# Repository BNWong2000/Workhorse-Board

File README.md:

# Workhorse-Board
Workhorse 3D printer controller board, intended for long term safe and reliable operation.

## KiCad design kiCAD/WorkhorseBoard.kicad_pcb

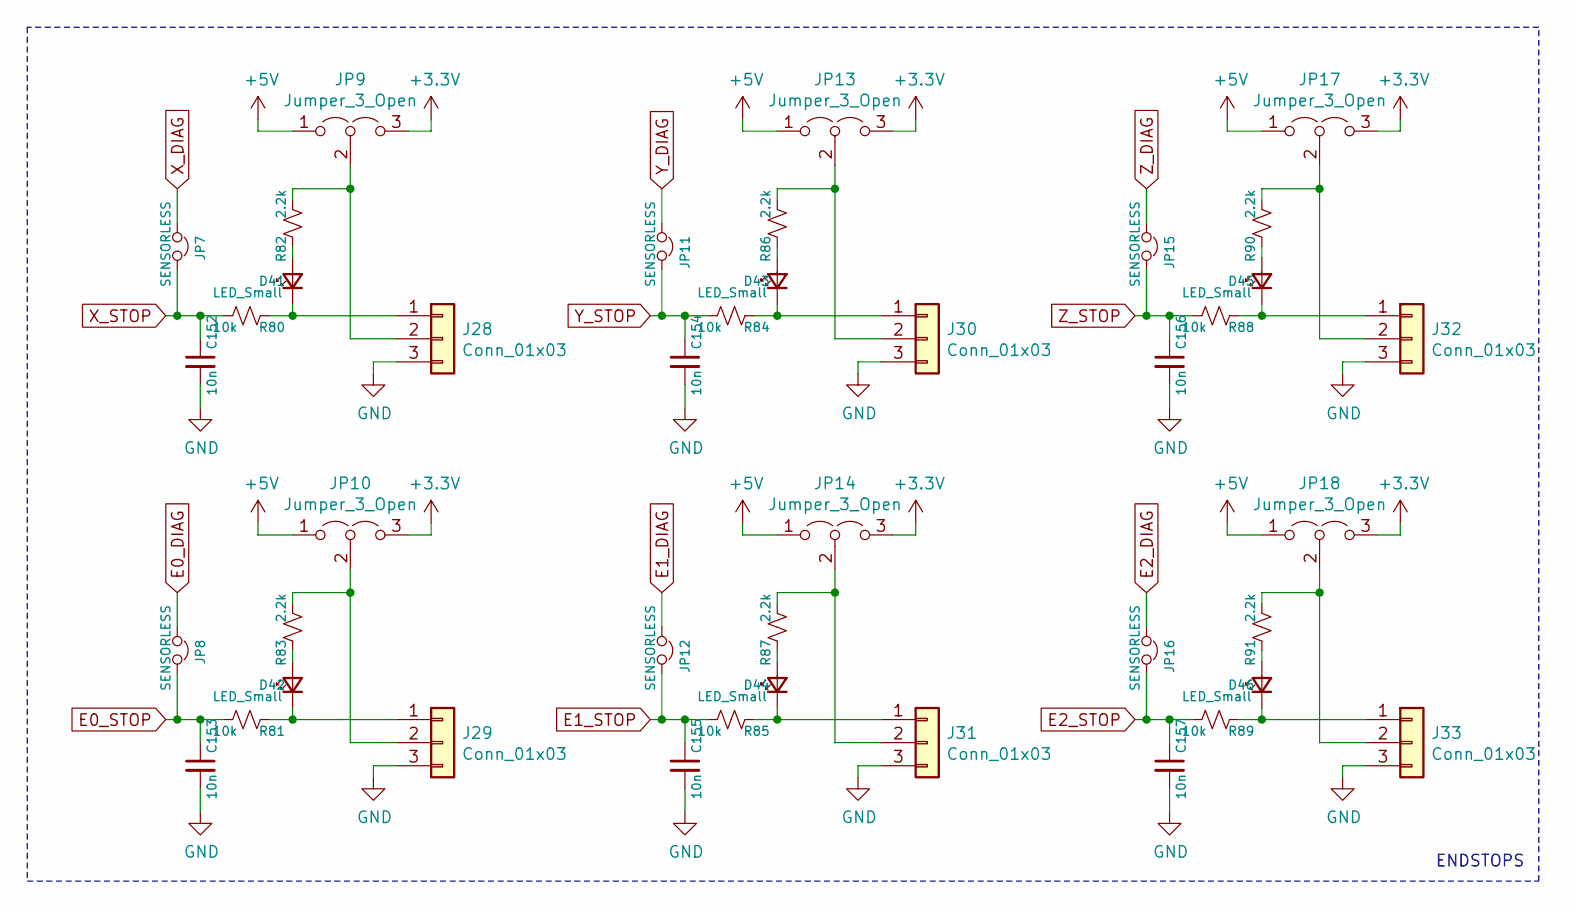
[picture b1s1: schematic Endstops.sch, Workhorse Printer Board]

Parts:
C152, C153, C154, C155, C156, C157: 10n; C_0603_1608Metric_Pad1.05x0.95mm_HandSolder
D41, D42, D43, D44, D45, D46: LED_Small; D_0603_1608Metric_Pad1.05x0.95mm_HandSolder
J28, J29, J30, J31, J32, J33: Conn_01x03; Molex_KK-254_AE-6410-03A_1x03_P2.54mm_Vertical
JP7, JP8, JP11, JP12, JP15, JP16: SENSORLESS; PinHeader_1x02_P2.54mm_Vertical
JP9, JP10, JP13, JP14, JP17, JP18: Jumper_3_Open; PinHeader_1x03_P2.54mm_Vertical
R80, R81, R84, R85, R88, R89: 10k; R_0603_1608Metric_Pad1.05x0.95mm_HandSolder
R82, R83, R86, R87, R90, R91: 2.2k; R_0603_1608Metric_Pad1.05x0.95mm_HandSolder

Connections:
+3V3: JP9.3 (B), JP10.3 (B), JP13.3 (B), JP14.3 (B), JP17.3 (B), JP18.3 (B); also elsewhere on the board
+5V: JP9.1 (A), JP10.1 (A), JP13.1 (A), JP14.1 (A), JP17.1 (A), JP18.1 (A); also elsewhere on the board
E0_DIAG: JP8.1; also elsewhere on the board
E0_STOP: C153.1, JP8.2, R81.2; also elsewhere on the board
E1_DIAG: JP12.1; also elsewhere on the board
E1_STOP: C155.1, JP12.2, R85.2; also elsewhere on the board
E2_DIAG: JP16.1; also elsewhere on the board
E2_STOP: C157.1, JP16.2, R89.2; also elsewhere on the board
GND: C152.2, C153.2, C154.2, C155.2, C156.2, C157.2, J28.3, J29.3, J30.3, J31.3, J32.3, J33.3; also elsewhere on the board
unnamed: D41.1 (K), J28.1, R80.1
unnamed: D41.2 (A), R82.1
unnamed: D42.1 (K), J29.1, R81.1
unnamed: D42.2 (A), R83.1
unnamed: D43.1 (K), J30.1, R84.1
unnamed: D43.2 (A), R86.1
unnamed: D44.1 (K), J31.1, R85.1
unnamed: D44.2 (A), R87.1
unnamed: D45.1 (K), J32.1, R88.1
unnamed: D45.2 (A), R90.1
unnamed: D46.1 (K), J33.1, R89.1
unnamed: D46.2 (A), R91.1
unnamed: J28.2, JP9.2 (C), R82.2
unnamed: J29.2, JP10.2 (C), R83.2
unnamed: J30.2, JP13.2 (C), R86.2
unnamed: J31.2, JP14.2 (C), R87.2
unnamed: J32.2, JP17.2 (C), R90.2
unnamed: J33.2, JP18.2 (C), R91.2
X_DIAG: JP7.1; also elsewhere on the board
X_STOP: C152.1, JP7.2, R80.2; also elsewhere on the board
Y_DIAG: JP11.1; also elsewhere on the board
Y_STOP: C154.1, JP11.2, R84.2; also elsewhere on the board
Z_DIAG: JP15.1; also elsewhere on the board
Z_STOP: C156.1, JP15.2, R88.2; also elsewhere on the board

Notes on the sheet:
ENDSTOPS

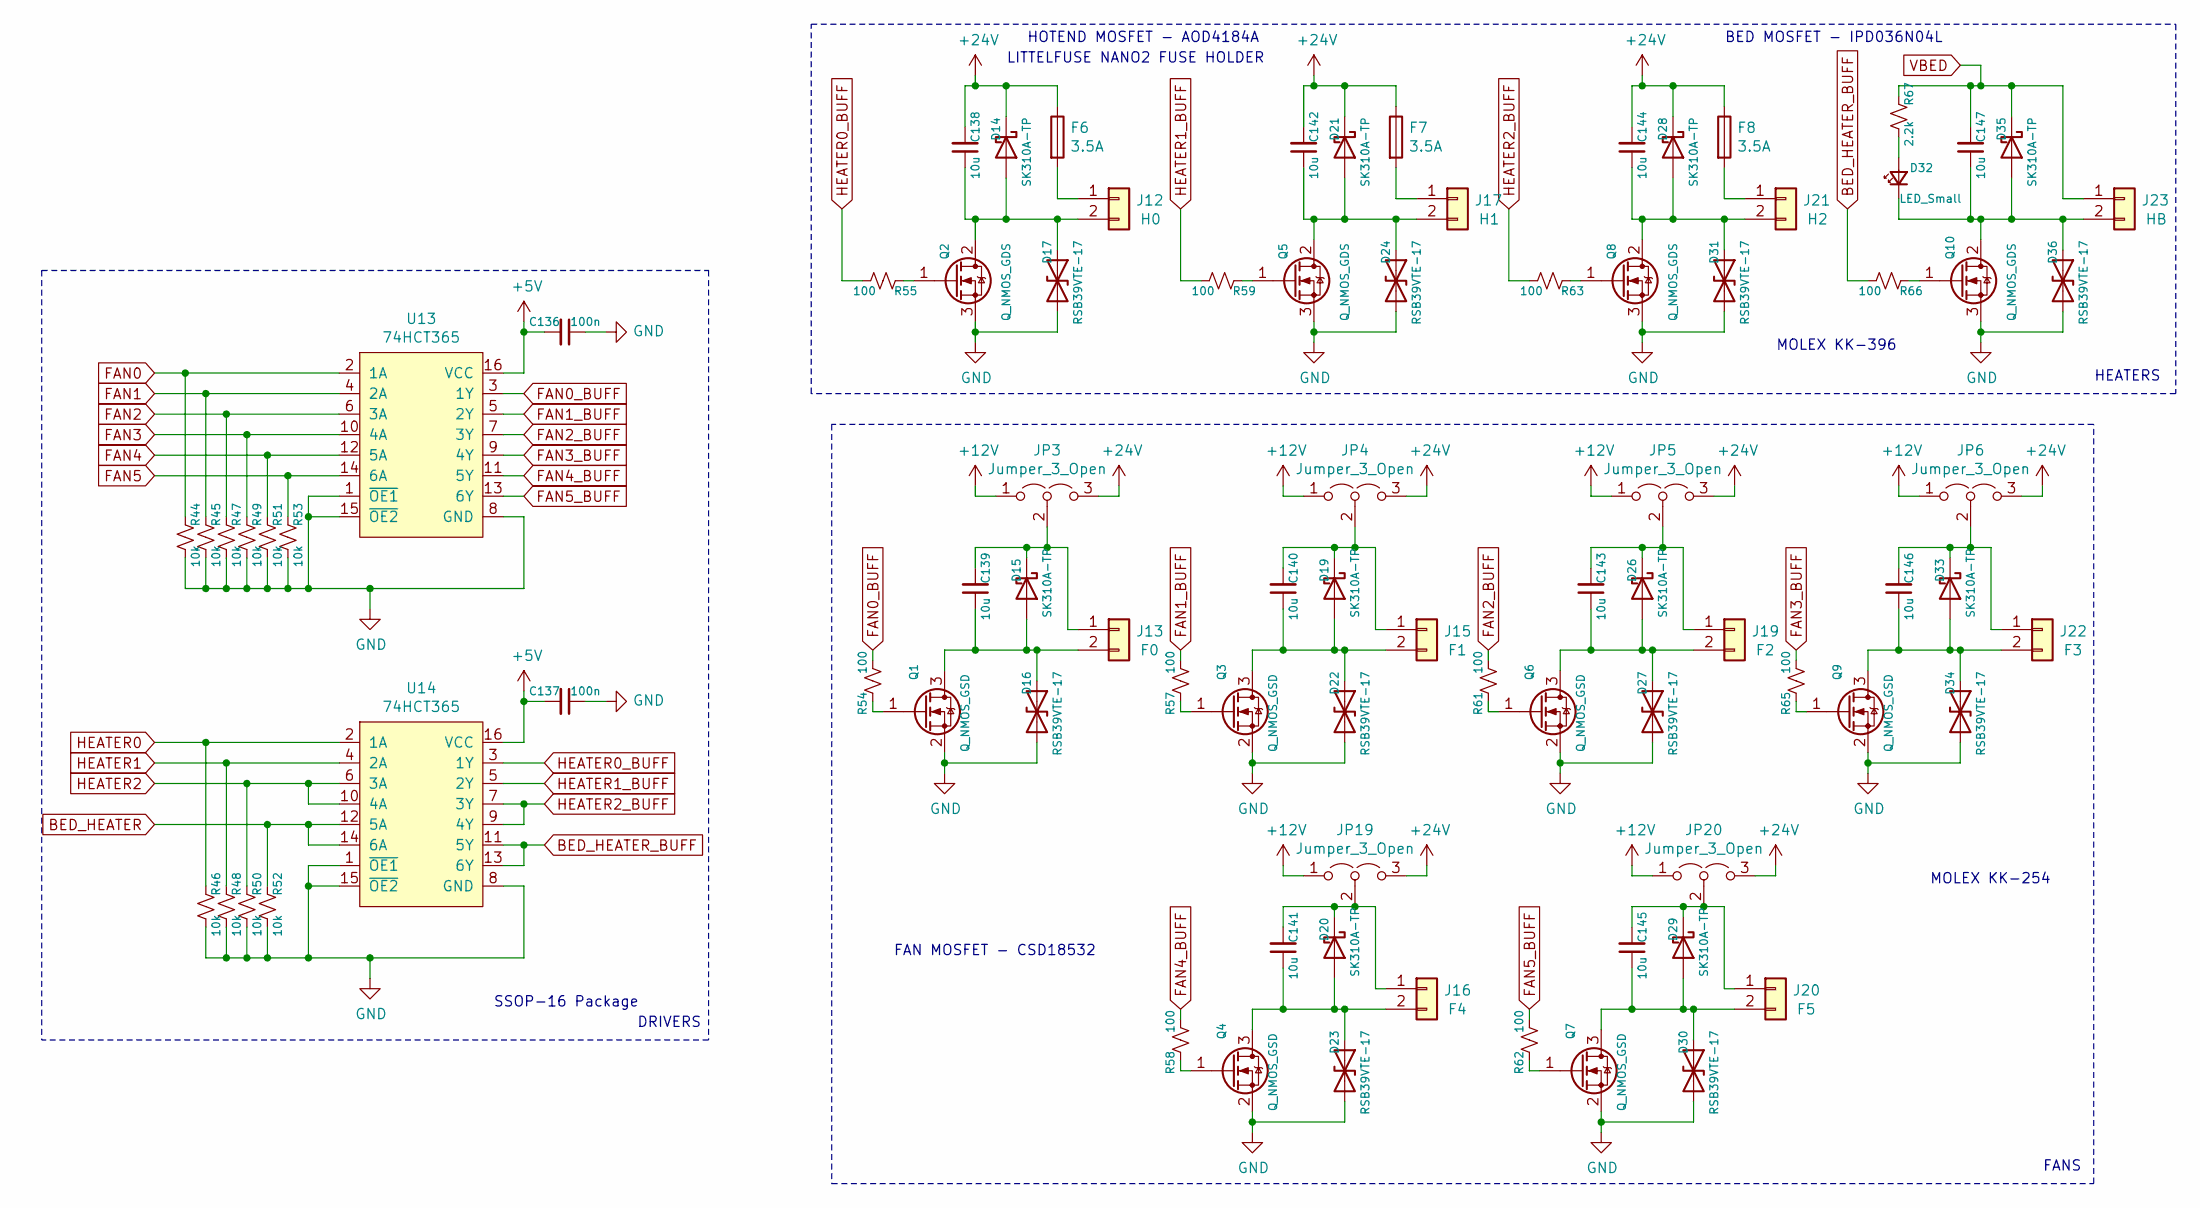
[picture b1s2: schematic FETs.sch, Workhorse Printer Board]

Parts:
C136, C137: 100n; C_0603_1608Metric_Pad1.05x0.95mm_HandSolder
C138, C139, C140, C141, C142, C143, C144, C145, C146, C147: 10u; C_1206_3216Metric_Pad1.42x1.75mm_HandSolder
D14, D15, D19, D20, D21, D26, D28, D29, D33, D35: SK310A-TP; D_SMA_Handsoldering
D16, D17, D22, D23, D24, D27, D30, D31, D34, D36: RSB39VTE-17; D_SOD-323F
D32: LED_Small; D_0603_1608Metric_Pad1.05x0.95mm_HandSolder
F6, F7, F8: 3.5A; Fuseholder_Littelfuse_Nano2_157x
J12: H0; Molex_KK-396_A-41791-0002_1x02_P3.96mm_Vertical
J13: F0; Molex_KK-254_AE-6410-02A_1x02_P2.54mm_Vertical
J15: F1; Molex_KK-254_AE-6410-02A_1x02_P2.54mm_Vertical
J16: F4; Molex_KK-254_AE-6410-02A_1x02_P2.54mm_Vertical
J17: H1; Molex_KK-396_A-41791-0002_1x02_P3.96mm_Vertical
J19: F2; Molex_KK-254_AE-6410-02A_1x02_P2.54mm_Vertical
J20: F5; Molex_KK-254_AE-6410-02A_1x02_P2.54mm_Vertical
J21: H2; Molex_KK-396_A-41791-0002_1x02_P3.96mm_Vertical
J22: F3; Molex_KK-254_AE-6410-02A_1x02_P2.54mm_Vertical
J23: HB; TerminalBlock_Dinkle_DT-55-B01X-02_P10.00mm
JP3, JP4, JP5, JP6, JP19, JP20: Jumper_3_Open; PinHeader_1x03_P2.54mm_Vertical
Q1, Q3, Q4, Q6, Q7, Q9: Q_NMOS_GSD; SOT-23_Handsoldering
Q2, Q5, Q8, Q10: Q_NMOS_GDS; TO-252-2
R44, R45, R46, R47, R48, R49, R50, R51, R52, R53: 10k; R_0603_1608Metric_Pad1.05x0.95mm_HandSolder
R54, R55, R57, R58, R59, R61, R62, R63, R65, R66: 100; R_0603_1608Metric_Pad1.05x0.95mm_HandSolder
R67: 2.2k; R_0603_1608Metric_Pad1.05x0.95mm_HandSolder
U13, U14: 74HCT365; SSOP-16_5.3x6.2mm_P0.65mm

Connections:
+5V: C136.2, C137.2, U13.16 (VCC), U14.16 (VCC); also elsewhere on the board
+12V: JP3.1 (A), JP4.1 (A), JP5.1 (A), JP6.1 (A), JP19.1 (A), JP20.1 (A); also elsewhere on the board
+24V: C138.2, C142.2, C144.2, D14.1 (K), D21.1 (K), D28.1 (K), F6.1, F7.1, F8.1, JP3.3 (B), JP4.3 (B), JP5.3 (B), JP6.3 (B), JP19.3 (B), JP20.3 (B); also elsewhere on the board
BED_HEATER: R52.1, U14.12 (5A), U14.14 (6A); also elsewhere on the board
BED_HEATER_BUFF: R66.2, U14.11 (5Y), U14.13 (6Y)
FAN0: R44.1, U13.2 (1A); also elsewhere on the board
FAN0_BUFF: R54.2, U13.3 (1Y)
FAN1: R45.1, U13.4 (2A); also elsewhere on the board
FAN1_BUFF: R57.2, U13.5 (2Y)
FAN2: R47.1, U13.6 (3A); also elsewhere on the board
FAN2_BUFF: R61.2, U13.7 (3Y)
FAN3: R49.1, U13.10 (4A); also elsewhere on the board
FAN3_BUFF: R65.2, U13.9 (4Y)
FAN4: R51.1, U13.12 (5A); also elsewhere on the board
FAN4_BUFF: R58.2, U13.11 (5Y)
FAN5: R53.1, U13.14 (6A); also elsewhere on the board
FAN5_BUFF: R62.2, U13.13 (6Y)
GND: C136.1, C137.1, D16.2 (A2), D17.2 (A2), D22.2 (A2), D23.2 (A2), D24.2 (A2), D27.2 (A2), D30.2 (A2), D31.2 (A2), D34.2 (A2), D36.2 (A2), Q1.2 (S), Q2.3 (S), Q3.2 (S), Q4.2 (S), Q5.3 (S), Q6.2 (S), Q7.2 (S), Q8.3 (S), Q9.2 (S), Q10.3 (S), R44.2, R45.2, R46.2, R47.2, R48.2, R49.2, R50.2, R51.2, R52.2, R53.2, U13.1 (~OE1), U13.8 (GND), U13.15 (~OE2), U14.1 (~OE1), U14.8 (GND), U14.15 (~OE2); also elsewhere on the board
HEATER0: R46.1, U14.2 (1A); also elsewhere on the board
HEATER0_BUFF: R55.2, U14.3 (1Y)
HEATER1: R48.1, U14.4 (2A); also elsewhere on the board
HEATER1_BUFF: R59.2, U14.5 (2Y)
HEATER2: R50.1, U14.6 (3A), U14.10 (4A); also elsewhere on the board
HEATER2_BUFF: R63.2, U14.7 (3Y), U14.9 (4Y)
unnamed: C138.1, D14.2 (A), D17.1 (A1), J12.2, Q2.2 (D)
unnamed: C139.1, D15.2 (A), D16.1 (A1), J13.2, Q1.3 (D)
unnamed: C139.2, D15.1 (K), J13.1, JP3.2 (C)
unnamed: C140.1, D19.2 (A), D22.1 (A1), J15.2, Q3.3 (D)
unnamed: C140.2, D19.1 (K), J15.1, JP4.2 (C)
unnamed: C141.1, D20.2 (A), D23.1 (A1), J16.2, Q4.3 (D)
unnamed: C141.2, D20.1 (K), J16.1, JP19.2 (C)
unnamed: C142.1, D21.2 (A), D24.1 (A1), J17.2, Q5.2 (D)
unnamed: C143.1, D26.2 (A), D27.1 (A1), J19.2, Q6.3 (D)
unnamed: C143.2, D26.1 (K), J19.1, JP5.2 (C)
unnamed: C144.1, D28.2 (A), D31.1 (A1), J21.2, Q8.2 (D)
unnamed: C145.1, D29.2 (A), D30.1 (A1), J20.2, Q7.3 (D)
unnamed: C145.2, D29.1 (K), J20.1, JP20.2 (C)
unnamed: C146.1, D33.2 (A), D34.1 (A1), J22.2, Q9.3 (D)
unnamed: C146.2, D33.1 (K), J22.1, JP6.2 (C)
unnamed: C147.1, D32.1 (K), D35.2 (A), D36.1 (A1), J23.2, Q10.2 (D)
unnamed: D32.2 (A), R67.2
unnamed: F6.2, J12.1
unnamed: F7.2, J17.1
unnamed: F8.2, J21.1
unnamed: Q1.1 (G), R54.1
unnamed: Q2.1 (G), R55.1
unnamed: Q3.1 (G), R57.1
unnamed: Q4.1 (G), R58.1
unnamed: Q5.1 (G), R59.1
unnamed: Q6.1 (G), R61.1
unnamed: Q7.1 (G), R62.1
unnamed: Q8.1 (G), R63.1
unnamed: Q9.1 (G), R65.1
unnamed: Q10.1 (G), R66.1
VBED: C147.2, D35.1 (K), J23.1, R67.1; also elsewhere on the board

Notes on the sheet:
BED MOSFET - IPD036N04L
HOTEND MOSFET - AOD4184A
FAN MOSFET - CSD18532
HEATERS
FANS
DRIVERS
LITTELFUSE NANO2 FUSE HOLDER
MOLEX KK-254
MOLEX KK-396
SSOP-16 Package

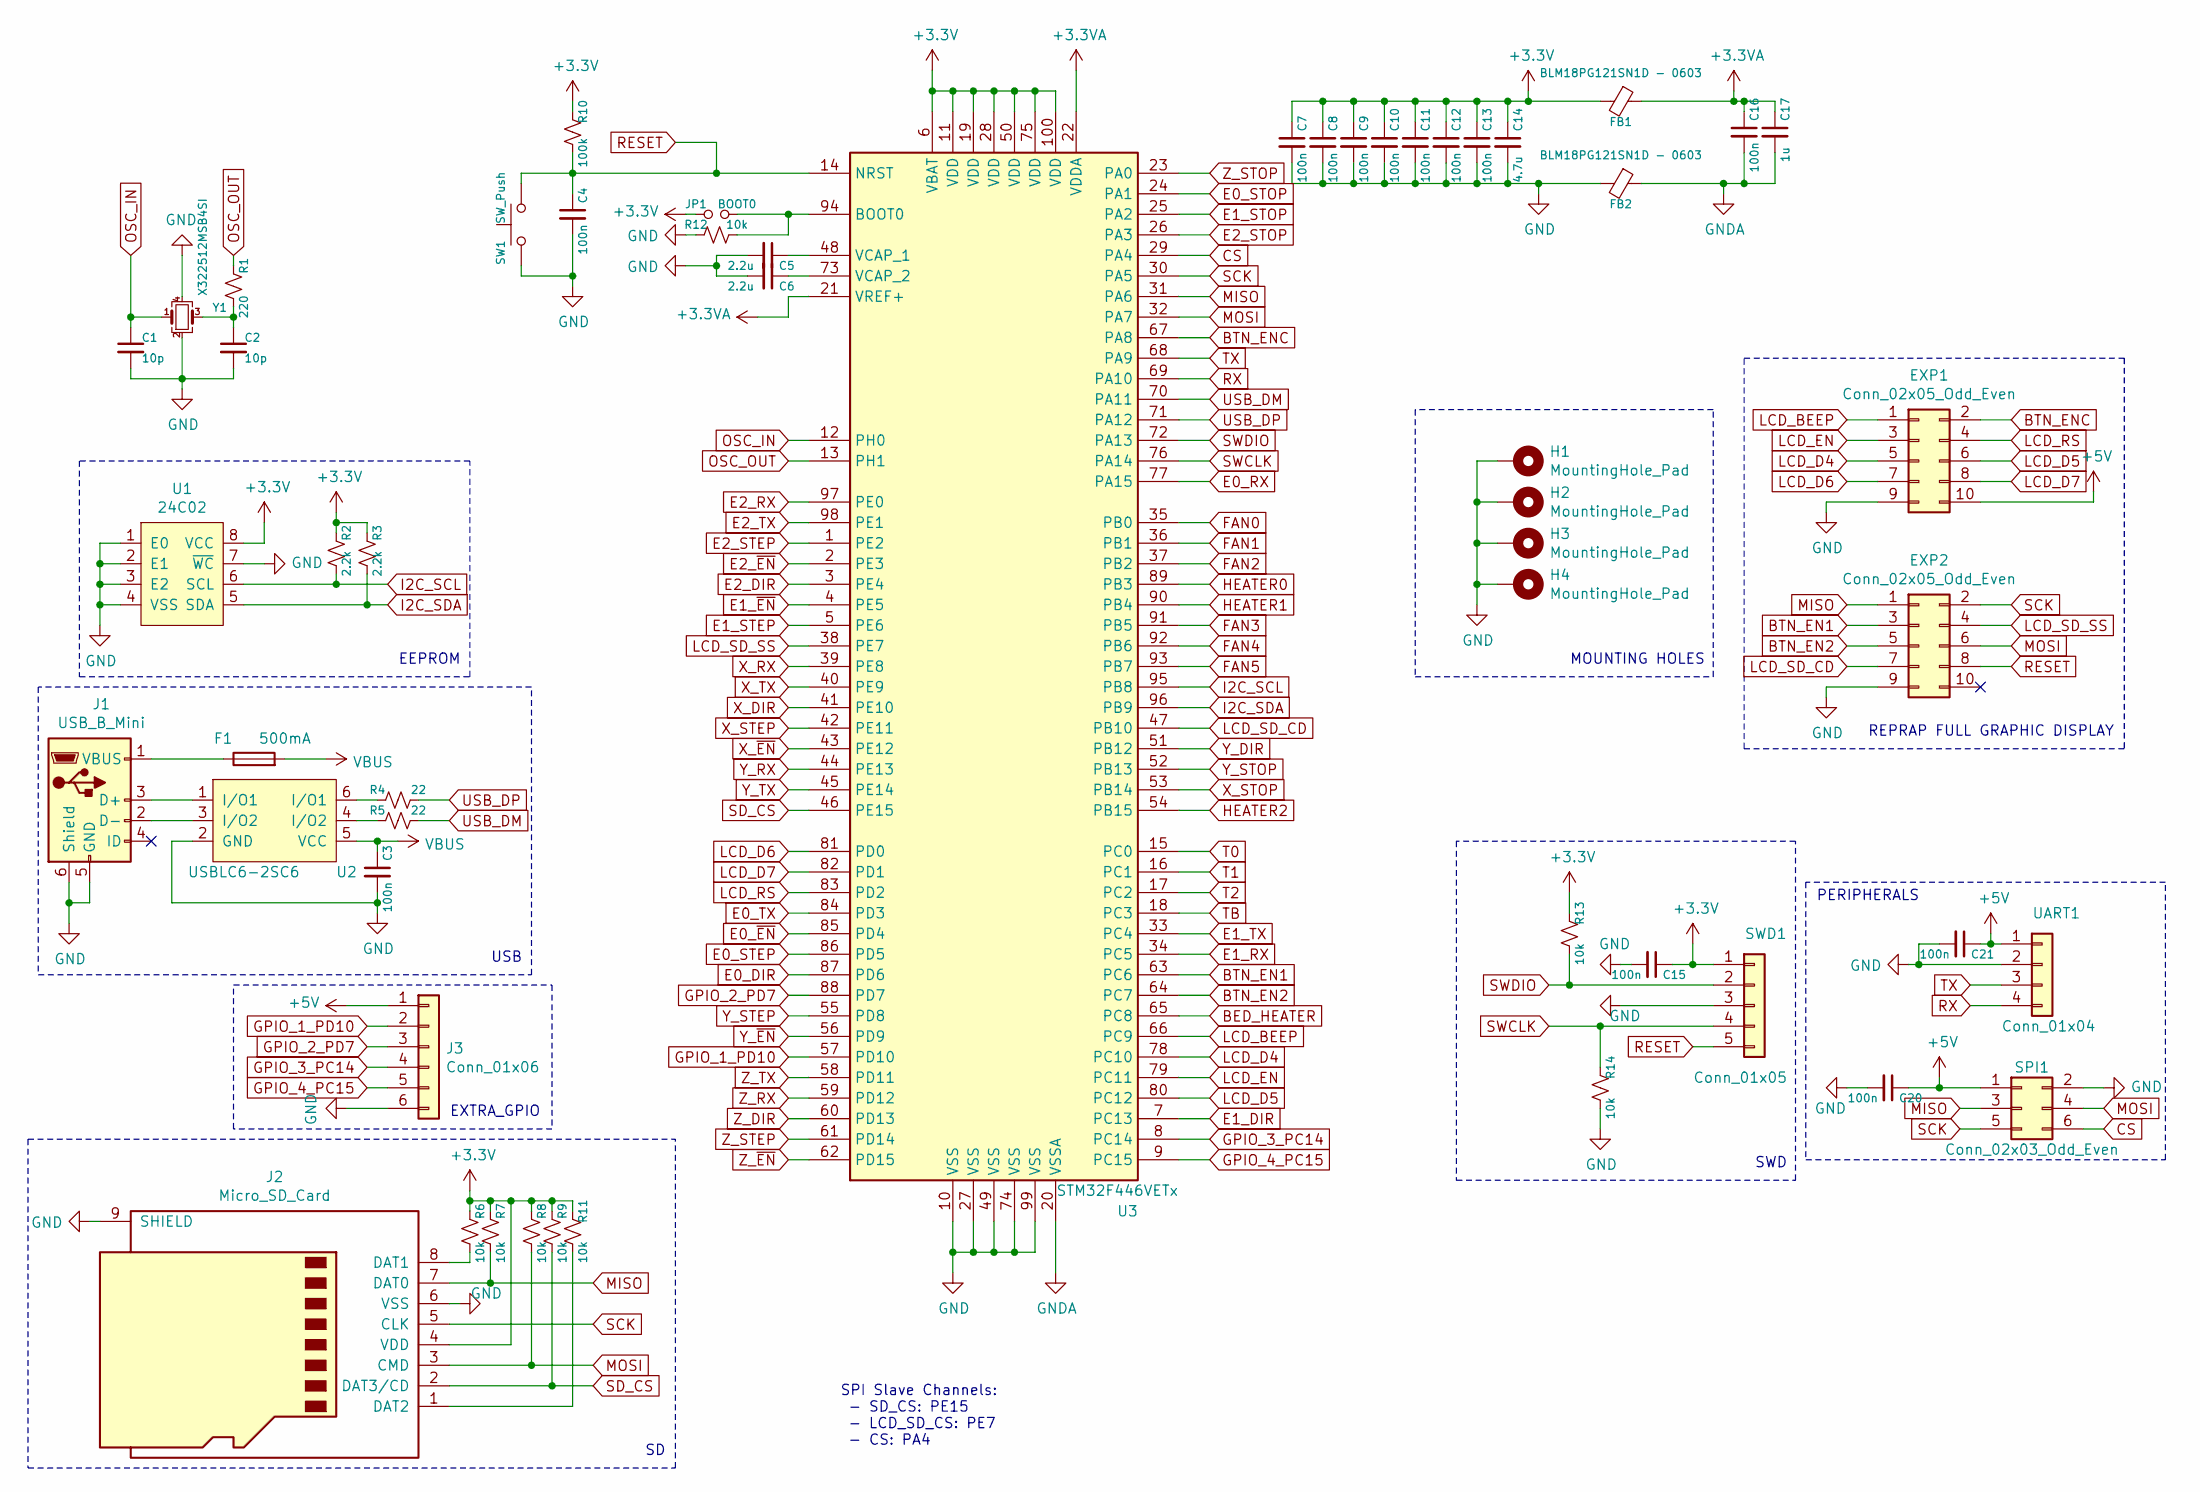
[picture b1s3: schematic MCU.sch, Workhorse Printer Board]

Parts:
C1, C2: 10p; C_0603_1608Metric_Pad1.05x0.95mm_HandSolder
C3, C4, C7, C8, C9, C10, C11, C12, C13, C15, C16, C20, C21: 100n; C_0603_1608Metric_Pad1.05x0.95mm_HandSolder
C5, C6: 2.2u; C_0805_2012Metric_Pad1.15x1.40mm_HandSolder
C14: 4.7u; C_0603_1608Metric_Pad1.05x0.95mm_HandSolder
C17: 1u; C_0603_1608Metric_Pad1.05x0.95mm_HandSolder
EXP1, EXP2: Conn_02x05_Odd_Even; PinHeader_2x05_P2.54mm_Vertical
F1: 500mA; Fuse_1812_4532Metric_Pad1.30x3.40mm_HandSolder
FB1, FB2: BLM18PG121SN1D - 0603; R_0201_0603Metric
H1, H2, H3, H4: MountingHole_Pad; MountingHole_4.3mm_M4_Pad_Via
J1: USB_B_Mini; USB_Mini-B_Lumberg_2486_01_Horizontal
J2: Micro_SD_Card; microSD_HC_Wuerth_693072010801
J3: Conn_01x06; PinSocket_1x06_P2.54mm_Vertical
JP1: BOOT0; PinHeader_1x02_P2.54mm_Vertical
R1: 220; R_0603_1608Metric_Pad1.05x0.95mm_HandSolder
R2, R3: 2.2k; R_0603_1608Metric_Pad1.05x0.95mm_HandSolder
R4, R5: 22; R_0603_1608Metric_Pad1.05x0.95mm_HandSolder
R6, R7, R8, R9, R11, R12, R13, R14: 10k; R_0603_1608Metric_Pad1.05x0.95mm_HandSolder
R10: 100k; R_0603_1608Metric_Pad1.05x0.95mm_HandSolder
SPI1: Conn_02x03_Odd_Even; PinHeader_2x03_P2.54mm_Vertical
SW1: SW_Push; SW_Push_1P1T_NO_6x6mm_H9.5mm
SWD1: Conn_01x05; PinHeader_1x05_P2.54mm_Vertical
U1: 24C02; SOIC-8_3.9x4.9mm_P1.27mm
U2: USBLC6-2SC6; SOT-23-6_Handsoldering
U3: STM32F446VETx; LQFP-100_14x14mm_P0.5mm
UART1: Conn_01x04; PinHeader_1x04_P2.54mm_Vertical
Y1: X322512MSB4SI; Crystal_SMD_3225-4Pin_3.2x2.5mm_HandSoldering

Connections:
+3.3VA: C16.1, C17.1, FB1.1, U3.21 (VREF+), U3.22 (VDDA)
+3V3: C7.1, C8.1, C9.1, C10.1, C11.1, C12.1, C13.1, C14.1, C15.1, FB1.2, J2.4 (VDD), JP1.1, R2.2, R3.2, R6.2, R7.2, R8.2, R9.2, R10.2, R11.2, R13.2, SWD1.1, U1.8 (VCC), U3.6 (VBAT), U3.11 (VDD), U3.19 (VDD), U3.28 (VDD), U3.50 (VDD), U3.75 (VDD), U3.100 (VDD); also elsewhere on the board
+5V: C20.1, C21.1, EXP1.10, J3.1, SPI1.1, UART1.1; also elsewhere on the board
BED_HEATER: U3.65 (PC8); also elsewhere on the board
BTN_EN1: EXP2.3, U3.63 (PC6)
BTN_EN2: EXP2.5, U3.64 (PC7)
BTN_ENC: EXP1.2, U3.67 (PA8)
CS: SPI1.6, U3.29 (PA4)
E0_DIR: U3.87 (PD6); also elsewhere on the board
E0_RX: U3.77 (PA15); also elsewhere on the board
E0_STEP: U3.86 (PD5); also elsewhere on the board
E0_STOP: U3.24 (PA1); also elsewhere on the board
E0_TX: U3.84 (PD3); also elsewhere on the board
E0_~EN: U3.85 (PD4); also elsewhere on the board
E1_DIR: U3.7 (PC13); also elsewhere on the board
E1_RX: U3.34 (PC5); also elsewhere on the board
E1_STEP: U3.5 (PE6); also elsewhere on the board
E1_STOP: U3.25 (PA2); also elsewhere on the board
E1_TX: U3.33 (PC4); also elsewhere on the board
E1_~EN: U3.4 (PE5); also elsewhere on the board
E2_DIR: U3.3 (PE4); also elsewhere on the board
E2_RX: U3.97 (PE0); also elsewhere on the board
E2_STEP: U3.1 (PE2); also elsewhere on the board
E2_STOP: U3.26 (PA3); also elsewhere on the board
E2_TX: U3.98 (PE1); also elsewhere on the board
E2_~EN: U3.2 (PE3); also elsewhere on the board
FAN0: U3.35 (PB0); also elsewhere on the board
FAN1: U3.36 (PB1); also elsewhere on the board
FAN2: U3.37 (PB2); also elsewhere on the board
FAN3: U3.91 (PB5); also elsewhere on the board
FAN4: U3.92 (PB6); also elsewhere on the board
FAN5: U3.93 (PB7); also elsewhere on the board
GND: C1.2, C2.2, C3.2, C4.2, C5.2, C6.2, C7.2, C8.2, C9.2, C10.2, C11.2, C12.2, C13.2, C14.2, C15.2, C20.2, C21.2, EXP1.9, EXP2.9, FB2.2, H1.1, H2.1, H3.1, H4.1, J1.5 (GND), J1.6 (Shield), J2.6 (VSS), J2.9 (SHIELD), J3.6, R12.2, R14.1, SPI1.2, SW1.1, SWD1.3, U1.1 (E0), U1.2 (E1), U1.3 (E2), U1.4 (VSS), U1.7 (~WC), U2.2 (GND), U3.10 (VSS), U3.27 (VSS), U3.49 (VSS), U3.74 (VSS), U3.99 (VSS), UART1.2, Y1.2, Y1.4; also elsewhere on the board
GNDA: C16.2, C17.2, FB2.1, U3.20 (VSSA)
GPIO_1_PD10: J3.2, U3.57 (PD10)
GPIO_2_PD7: J3.3, U3.88 (PD7)
GPIO_3_PC14: J3.4, U3.8 (PC14)
GPIO_4_PC15: J3.5, U3.9 (PC15)
HEATER0: U3.89 (PB3); also elsewhere on the board
HEATER1: U3.90 (PB4); also elsewhere on the board
HEATER2: U3.54 (PB15); also elsewhere on the board
I2C_SCL: R2.1, U1.6 (SCL), U3.95 (PB8)
I2C_SDA: R3.1, U1.5 (SDA), U3.96 (PB9)
LCD_BEEP: EXP1.1, U3.66 (PC9)
LCD_D4: EXP1.5, U3.78 (PC10)
LCD_D5: EXP1.6, U3.80 (PC12)
LCD_D6: EXP1.7, U3.81 (PD0)
LCD_D7: EXP1.8, U3.82 (PD1)
LCD_EN: EXP1.3, U3.79 (PC11)
LCD_RS: EXP1.4, U3.83 (PD2)
LCD_SD_CD: EXP2.7, U3.47 (PB10)
LCD_SD_SS: EXP2.4, U3.38 (PE7)
MISO: EXP2.1, J2.7 (DAT0), R7.1, SPI1.3, U3.31 (PA6)
MOSI: EXP2.6, J2.3 (CMD), R8.1, SPI1.4, U3.32 (PA7)
unnamed: C2.1, R1.1, Y1.3
unnamed: C5.1, U3.48 (VCAP_1)
unnamed: C6.1, U3.73 (VCAP_2)
unnamed: F1.1, J1.1 (VBUS)
unnamed: J1.2 (D-), U2.3 (I/O2)
unnamed: J1.3 (D+), U2.1 (I/O1)
unnamed: J2.1 (DAT2), R11.1
unnamed: J2.8 (DAT1), R6.1
unnamed: JP1.2, R12.1, U3.94 (BOOT0)
unnamed: R4.2, U2.6 (I/O1)
unnamed: R5.2, U2.4 (I/O2)
OSC_IN: C1.1, U3.12 (PH0), Y1.1
OSC_OUT: R1.2, U3.13 (PH1)
RESET: C4.1, EXP2.8, R10.1, SW1.2, SWD1.5, U3.14 (NRST)
RX: U3.69 (PA10), UART1.4
SCK: EXP2.2, J2.5 (CLK), SPI1.5, U3.30 (PA5)
SD_CS: J2.2 (DAT3/CD), R9.1, U3.46 (PE15)
SWCLK: R14.2, SWD1.4, U3.76 (PA14)
SWDIO: R13.1, SWD1.2, U3.72 (PA13)
T0: U3.15 (PC0); also elsewhere on the board
T1: U3.16 (PC1); also elsewhere on the board
T2: U3.17 (PC2); also elsewhere on the board
TB: U3.18 (PC3); also elsewhere on the board
TX: U3.68 (PA9), UART1.3
USB_DM: R5.1, U3.70 (PA11)
USB_DP: R4.1, U3.71 (PA12)
VBUS: C3.1, F1.2, U2.5 (VCC); also elsewhere on the board
X_DIR: U3.41 (PE10); also elsewhere on the board
X_RX: U3.39 (PE8); also elsewhere on the board
X_STEP: U3.42 (PE11); also elsewhere on the board
X_STOP: U3.53 (PB14); also elsewhere on the board
X_TX: U3.40 (PE9); also elsewhere on the board
X_~EN: U3.43 (PE12); also elsewhere on the board
Y_DIR: U3.51 (PB12); also elsewhere on the board
Y_RX: U3.44 (PE13); also elsewhere on the board
Y_STEP: U3.55 (PD8); also elsewhere on the board
Y_STOP: U3.52 (PB13); also elsewhere on the board
Y_TX: U3.45 (PE14); also elsewhere on the board
Y_~EN: U3.56 (PD9); also elsewhere on the board
Z_DIR: U3.60 (PD13); also elsewhere on the board
Z_RX: U3.59 (PD12); also elsewhere on the board
Z_STEP: U3.61 (PD14); also elsewhere on the board
Z_STOP: U3.23 (PA0); also elsewhere on the board
Z_TX: U3.58 (PD11); also elsewhere on the board
Z_~EN: U3.62 (PD15); also elsewhere on the board

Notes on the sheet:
SWD
USB
EEPROM
PERIPHERALS
SPI Slave Channels: - SD_CS: PE15 - LCD_SD_CS: PE7 - CS: PA4
REPRAP FULL GRAPHIC DISPLAY
EXTRA_GPIO
MOUNTING HOLES

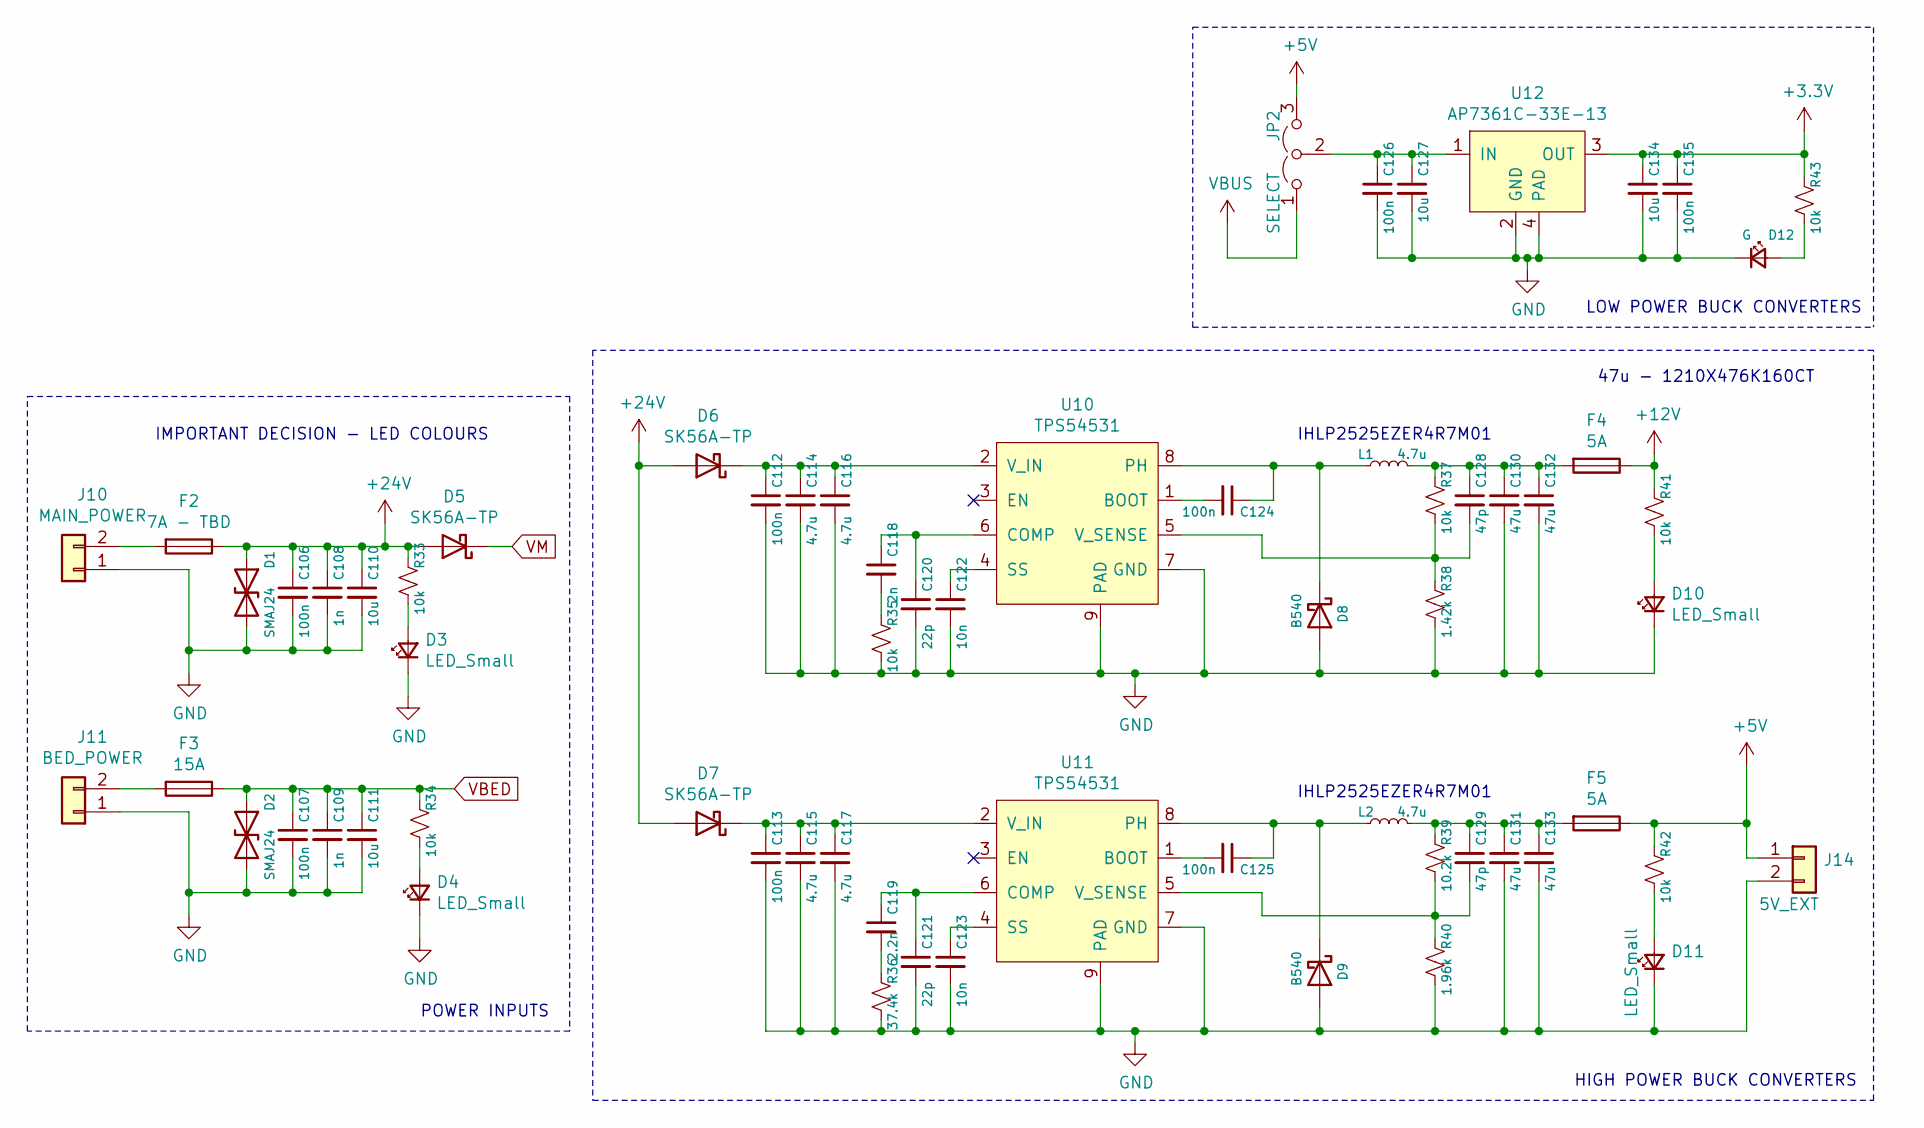
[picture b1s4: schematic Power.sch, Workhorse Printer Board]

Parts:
C106, C107, C112, C113, C124, C125, C126, C135: 100n; C_0603_1608Metric_Pad1.05x0.95mm_HandSolder
C108, C109: 1n; C_0603_1608Metric_Pad1.05x0.95mm_HandSolder
C110, C111, C127, C134: 10u; C_1206_3216Metric_Pad1.42x1.75mm_HandSolder
C114, C115, C116, C117: 4.7u; C_0603_1608Metric_Pad1.05x0.95mm_HandSolder
C118: 2n; C_0603_1608Metric_Pad1.05x0.95mm_HandSolder
C119: 2.2n; C_0603_1608Metric_Pad1.05x0.95mm_HandSolder
C120, C121: 22p; C_0603_1608Metric_Pad1.05x0.95mm_HandSolder
C122, C123: 10n; C_0603_1608Metric_Pad1.05x0.95mm_HandSolder
C128, C129: 47p; C_0603_1608Metric_Pad1.05x0.95mm_HandSolder
C130, C131, C132, C133: 47u; C_1210_3225Metric_Pad1.42x2.65mm_HandSolder
D1, D2: SMAJ24; D_SMA_Handsoldering
D3, D4, D10, D11: LED_Small; D_0603_1608Metric_Pad1.05x0.95mm_HandSolder
D5, D6, D7: SK56A-TP; D_SMA_Handsoldering
D8, D9: B540; D_SMC_Handsoldering
D12: G; D_0603_1608Metric_Pad1.05x0.95mm_HandSolder
F2: 7A - TBD; Fuseholder_Blade_Mini_Keystone_3568
F3: 15A; Fuseholder_Blade_Mini_Keystone_3568
F4, F5: 5A; Fuse_2920_7451Metric_Pad2.10x5.45mm_HandSolder
J10: MAIN_POWER; TerminalBlock_Dinkle_DT-55-B01X-02_P10.00mm
J11: BED_POWER; TerminalBlock_Dinkle_DT-55-B01X-02_P10.00mm
J14: 5V_EXT; Molex_KK-254_AE-6410-02A_1x02_P2.54mm_Vertical
JP2: SELECT; PinHeader_1x03_P2.54mm_Vertical
L1, L2: 4.7u; L_Vishay_IHLP-2525
R33, R34, R35, R37, R41, R42, R43: 10k; R_0603_1608Metric_Pad1.05x0.95mm_HandSolder
R36: 37.4k; R_0603_1608Metric_Pad1.05x0.95mm_HandSolder
R38: 1.42k; R_0603_1608Metric_Pad1.05x0.95mm_HandSolder
R39: 10.2k; R_0603_1608Metric_Pad1.05x0.95mm_HandSolder
R40: 1.96k; R_0603_1608Metric_Pad1.05x0.95mm_HandSolder
U10, U11: TPS54531; TI_SO-PowerPAD-8_ThermalVias
U12: AP7361C-33E-13; SOT-223

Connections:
+3V3: C134.1, C135.1, R43.1, U12.3 (OUT); also elsewhere on the board
+5V: F5.1, J14.1, JP2.3 (B), R42.1; also elsewhere on the board
+12V: F4.1, R41.1; also elsewhere on the board
+24V: C106.1, C108.1, C110.1, D1.1 (A1), D5.2 (A), D6.2 (A), D7.2 (A), F2.1, R33.1; also elsewhere on the board
GND: C106.2, C107.2, C108.2, C109.2, C110.2, C111.2, C112.2, C113.2, C114.2, C115.2, C116.2, C117.2, C120.2, C121.2, C122.2, C123.2, C126.2, C127.2, C130.2, C131.2, C132.2, C133.2, C134.2, C135.2, D1.2 (A2), D2.2 (A2), D3.1 (K), D4.1 (K), D8.2 (A), D9.2 (A), D10.1 (K), D11.1 (K), D12.1 (K), J10.1, J11.1, J14.2, R35.2, R36.2, R38.2, R40.2, U10.7 (GND), U10.9 (PAD), U11.7 (GND), U11.9 (PAD), U12.2 (GND), U12.4 (PAD); also elsewhere on the board
unnamed: C112.1, C114.1, C116.1, D6.1 (K), U10.2 (V_IN)
unnamed: C113.1, C115.1, C117.1, D7.1 (K), U11.2 (V_IN)
unnamed: C118.1, C120.1, U10.6 (COMP)
unnamed: C118.2, R35.1
unnamed: C119.1, C121.1, U11.6 (COMP)
unnamed: C119.2, R36.1
unnamed: C122.1, U10.4 (SS)
unnamed: C123.1, U11.4 (SS)
unnamed: C124.1, D8.1 (K), L1.1, U10.8 (PH)
unnamed: C124.2, U10.1 (BOOT)
unnamed: C125.1, D9.1 (K), L2.1, U11.8 (PH)
unnamed: C125.2, U11.1 (BOOT)
unnamed: C126.1, C127.1, JP2.2 (C), U12.1 (IN)
unnamed: C128.1, C130.1, C132.1, F4.2, L1.2, R37.1
unnamed: C128.2, R37.2, R38.1, U10.5 (V_SENSE)
unnamed: C129.1, C131.1, C133.1, F5.2, L2.2, R39.1
unnamed: C129.2, R39.2, R40.1, U11.5 (V_SENSE)
unnamed: D3.2 (A), R33.2
unnamed: D4.2 (A), R34.2
unnamed: D10.2 (A), R41.2
unnamed: D11.2 (A), R42.2
unnamed: D12.2 (A), R43.2
unnamed: F2.2, J10.2
unnamed: F3.2, J11.2
VBED: C107.1, C109.1, C111.1, D2.1 (A1), F3.1, R34.1; also elsewhere on the board
VBUS: JP2.1 (A); also elsewhere on the board
VM: D5.1 (K); also elsewhere on the board

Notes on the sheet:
POWER INPUTS
LOW POWER BUCK CONVERTERS
HIGH POWER BUCK CONVERTERS
IMPORTANT DECISION - LED COLOURS
IHLP2525EZER4R7M01
47u - 1210X476K160CT
